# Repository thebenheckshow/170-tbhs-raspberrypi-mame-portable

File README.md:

# 170-tbhs-raspberrypi-mame-portable

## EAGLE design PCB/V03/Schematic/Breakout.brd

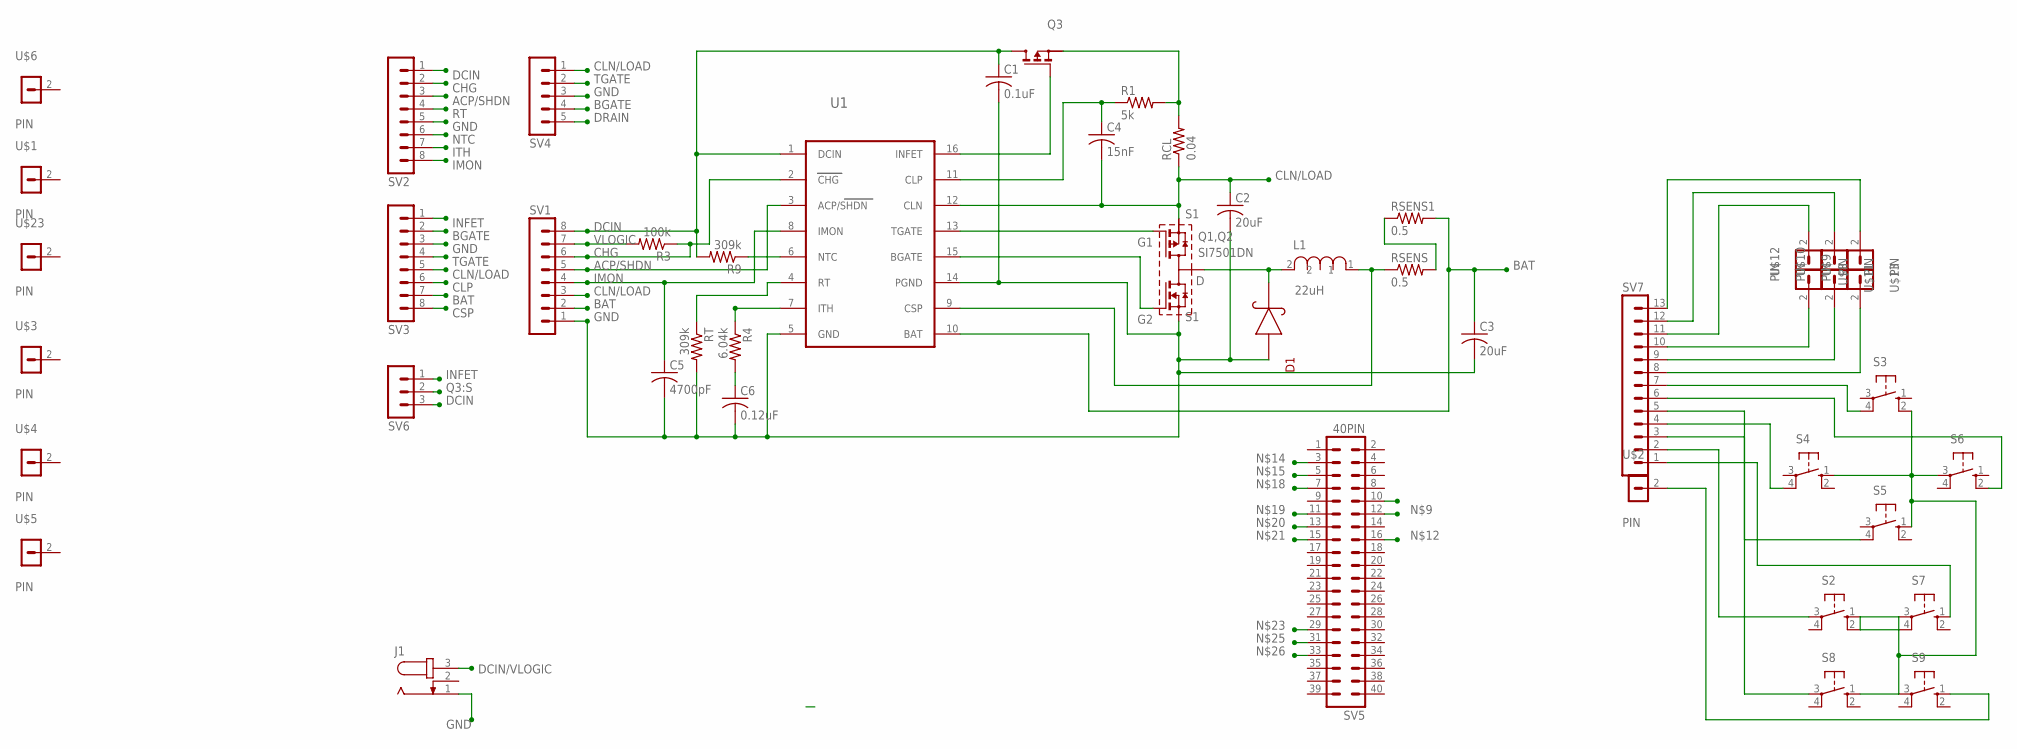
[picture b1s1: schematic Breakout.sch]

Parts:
C1: 0.1uF; C1210
C2, C3: 20uF; C1210
C4: 15nF; C1210
C5: 4700pF; C1210
C6: 0.12uF; C1210
D1: DIODE
J1: JACK-PLUG0; SPC4077
L1: 22uH; POWERINDUCTOR
Q1,Q2: SI7501DN; POWERPAK
Q3: MOSFET; SOT-23
R1: 5k; R1206
R3: 100k; R1206
R4: 6.04k; R1206
R9: 309k; R1206
RCL: 0.04; R1206
RSENS, RSENS1: 0.5; 0612/1632
RT: 309k; R1206
S2, S3, S4, S5, S6, S7, S8, S9: 10-XX; B3F-10XX
SV1, SV2, SV3: MA08-1
SV4: MA05-1
SV5: 40PIN; 40PINHEADDER
SV6: MA03-1
SV7: MA13-1
U1: LTC6004; SSOP-16
U$1, U$2, U$3, U$4, U$5, U$6, U$8, U$9, U$10, U$11, U$12, U$13, U$23: PIN

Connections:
ACP/SHDN: SV1.5, SV2.3, U1.3 (ACP/SHDN)
BAT: C3.1, RSENS1.2, SV1.2, SV3.7, U1.10 (BAT)
BGATE: Q1,Q2.G2, SV3.2, SV4.4, U1.15 (BGATE)
CHG: R3.1, SV1.6, SV2.2, U1.2 (CHG)
CLN/LOAD: C2.1, C4.2, Q1,Q2.S1, RCL.1, SV1.3, SV3.5, SV4.1, U1.12 (CLN)
CLP: C4.1, R1.1, SV3.6, U1.11 (CLP)
CSP: L1.1, RSENS.1, SV3.8, U1.9 (CSP)
DCIN: C1.1, Q3.DRAIN (D), R9.2, SV1.8, SV2.1, SV6.3, U1.1 (DCIN)
DCIN/VLOGIC: J1.3
DRAIN: D1.P$1 (2), L1.2, Q1,Q2.D, SV4.5
GND: C1.2, C2.2, C3.2, C5.2, C6.2, D1.P$2 (1), J1.1, Q1,Q2.S2, RT.2, S2.1 (S), S2.2 (S1), S3.2 (S1), S4.1 (S), S5.1 (S), S6.3, S7.3, S7.4 (P1), S8.1 (S), S9.3, SV1.1, SV2.5, SV3.3, SV4.3, U1.5 (GND), U1.14 (PGND)
IMON: C5.1, SV1.4, SV2.8, U1.8 (IMON)
INFET: Q3.GATE (G), SV3.1, SV6.1, U1.16 (INFET)
ITH: R4.1, SV2.7, U1.7 (ITH)
unnamed: RSENS.2, RSENS1.1
unnamed: SV7.13, U$9.2
unnamed: SV7.12, U$10.2
unnamed: C6.1, R4.2
unnamed: SV7.11, U$12.2
unnamed: SV7.10, U$8.2
unnamed: SV7.9, U$11.2
unnamed: SV7.8, U$13.2
unnamed: S3.4 (P1), SV7.7
unnamed: S6.2 (S1), SV7.6
unnamed: S4.4 (P1), SV7.4
unnamed: S5.4 (P1), SV7.5
unnamed: S8.3, SV7.3
unnamed: S2.3, SV7.2
unnamed: S7.1 (S), SV7.1
unnamed: S9.1 (S), U$2.2
NTC: R9.1, SV2.6, U1.6 (NTC)
Q3:S: Q3.SOURCE (S), R1.2, RCL.2, SV6.2
RT: RT.1, SV2.4, U1.4 (RT)
TGATE: Q1,Q2.G1, SV3.4, SV4.2, U1.13 (TGATE)
VLOGIC: R3.2, SV1.7

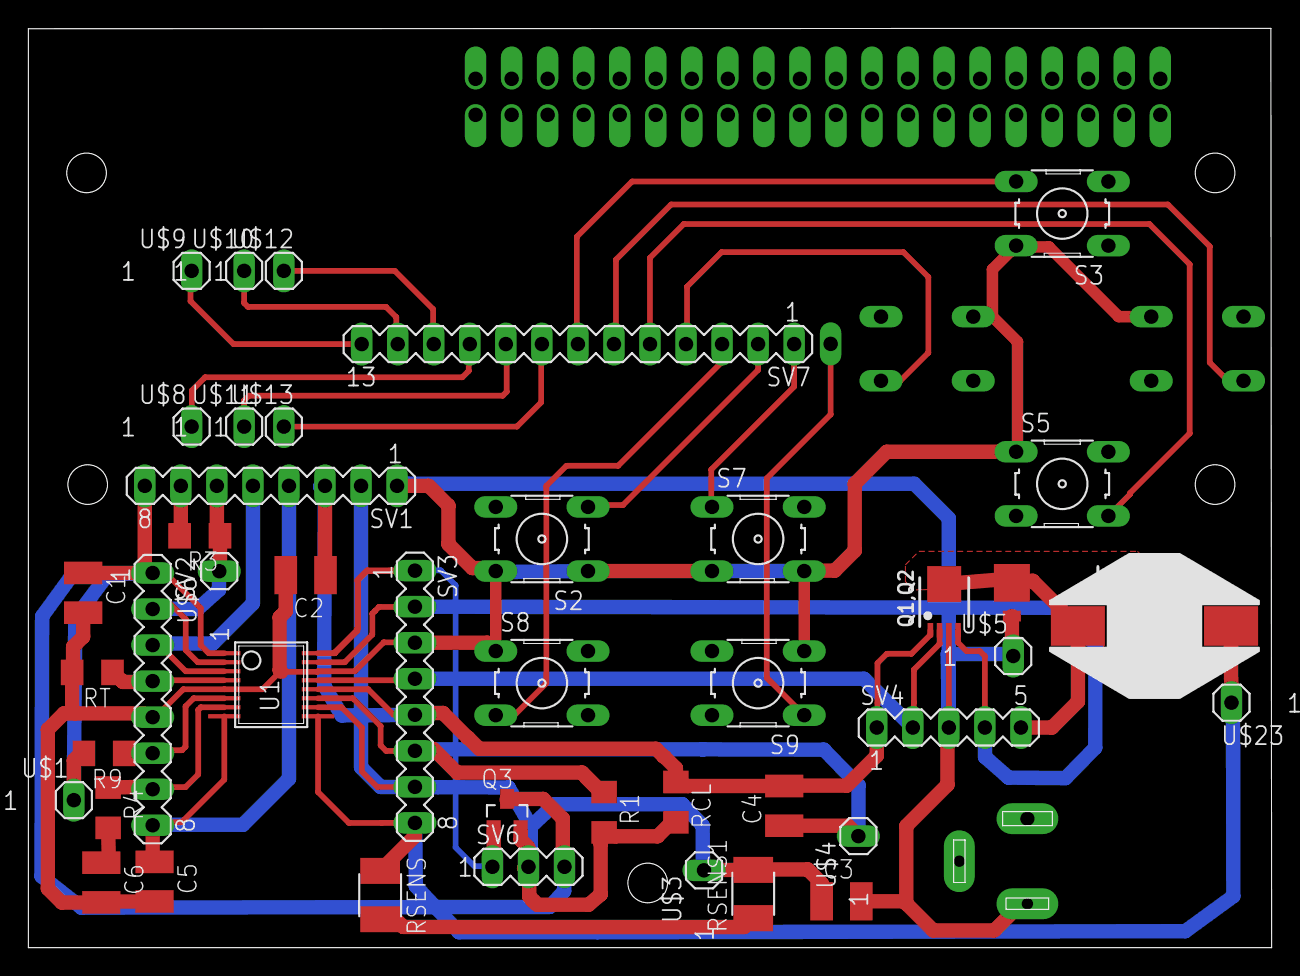
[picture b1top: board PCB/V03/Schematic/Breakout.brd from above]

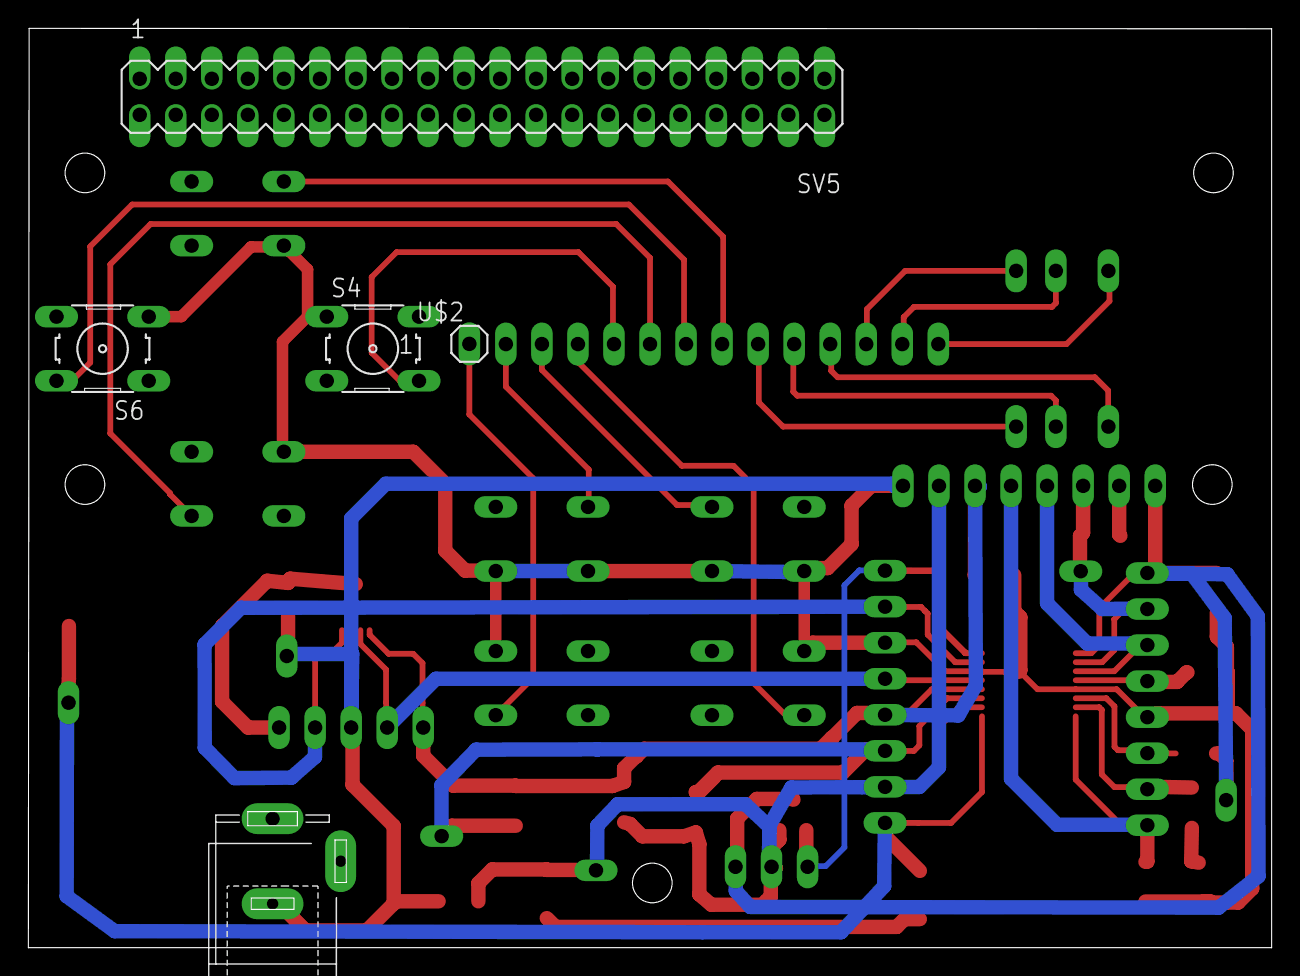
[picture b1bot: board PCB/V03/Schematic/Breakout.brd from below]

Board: 2 copper layers, 87.6 x 64.8 mm, 48 parts (5 on the bottom side), 34 nets.

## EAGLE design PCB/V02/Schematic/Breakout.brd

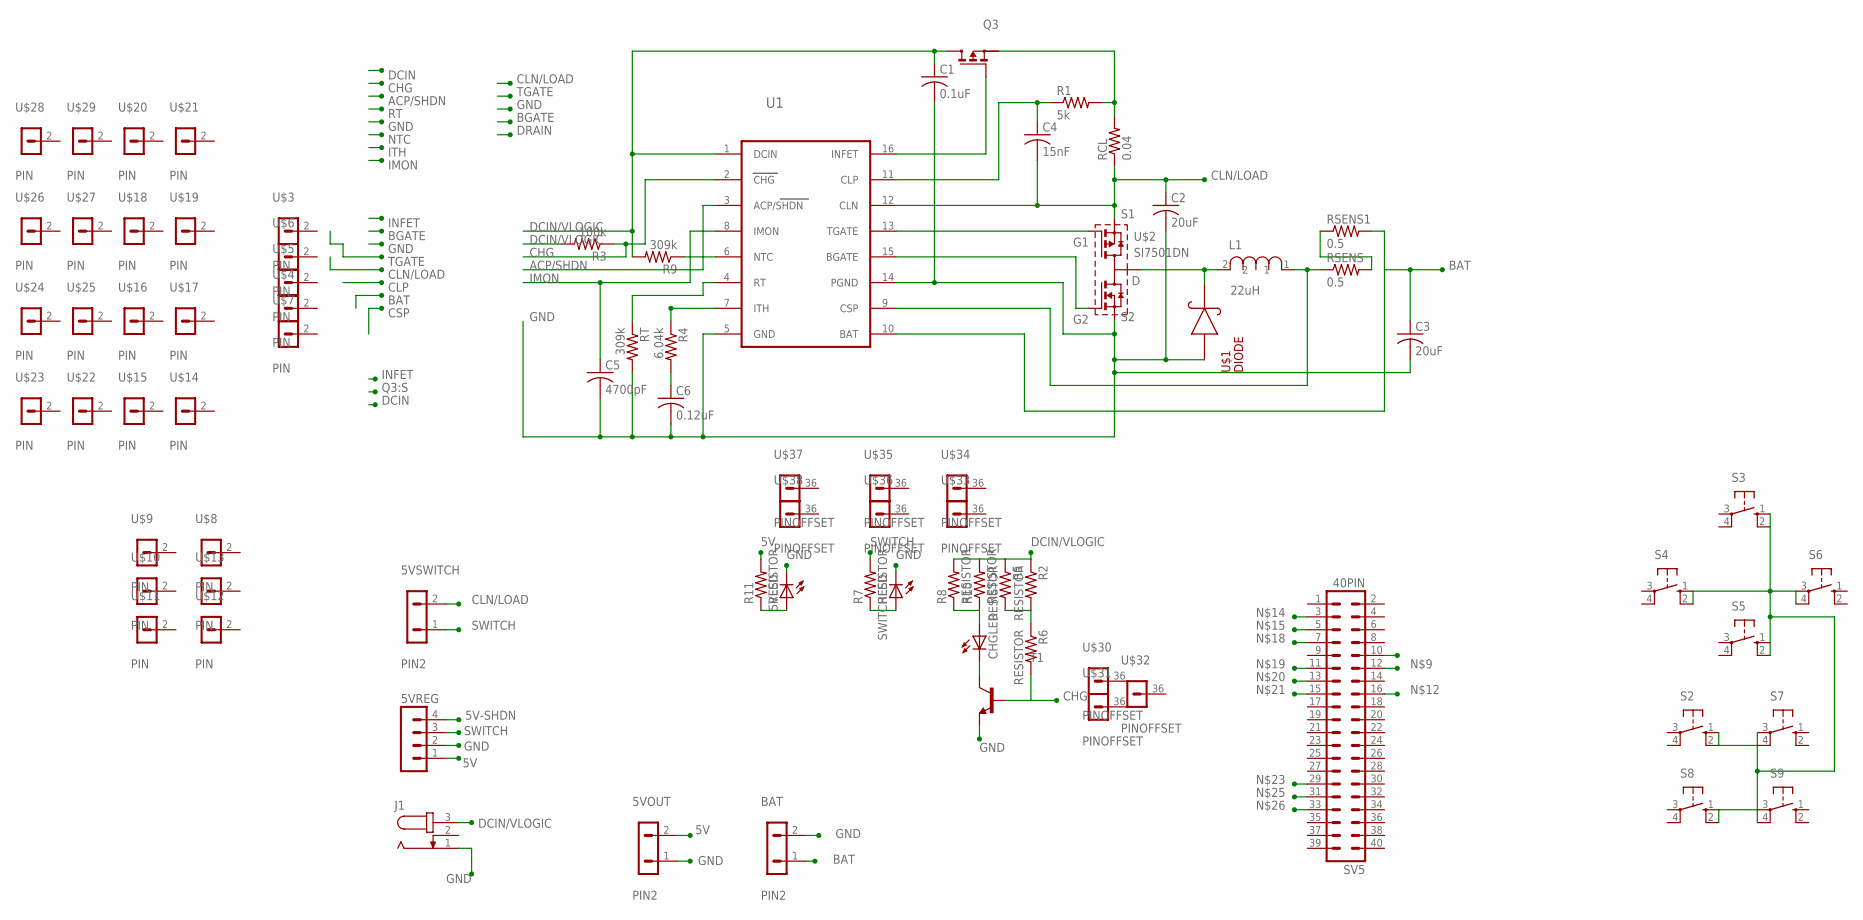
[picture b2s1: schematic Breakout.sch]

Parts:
5VLED: LED5MM
5VOUT, 5VSWITCH: PIN2
5VREG: MA04-1
BAT: PIN2
C1: 0.1uF; C1210
C2, C3: 20uF; C1210
C4: 15nF; C1210
C5: 4700pF; C1210
C6: 0.12uF; C1210
CHGLED: LED5MM
J1: JACK-PLUG0; SPC4077
L1: 22uH; POWERINDUCTOR
Q3: MOSFET; SOT-23
R1: 5k; R1206
R2, R5, R6, R7, R8, R10, R11: RESISTOR
R3: 100k; R1206
R4: 6.04k; R1206
R9: 309k; R1206
RCL: 0.04; R1206
RSENS, RSENS1: 0.5; 0612/1632
RT: 309k; R1206
S2, S3, S4, S5, S6, S7, S8, S9: 10-XX; B3F-10XX
SV5: 40PIN; 40PINHEADDER
SWITCHLED: LED5MM
T1: -NPN-TO92-E1; TO92-E1
U1: LTC6004; SSOP-16
U$1: DIODE
U$2: SI7501DN; POWERPAK
U$3, U$4, U$5, U$6, U$7, U$8, U$9, U$10, U$11, U$12, U$13, U$14, U$15, U$16, U$17, U$18, U$19, U$20, U$21, U$22, U$23, U$24, U$25, U$26, U$27, U$28, U$29: PIN
U$30, U$31, U$32, U$33, U$34, U$35, U$36, U$37, U$38: PINOFFSET; PINOFFST

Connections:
5V: 5VOUT.2, 5VREG.1, R11.1 (2)
5V-SHDN: 5VREG.4
ACP/SHDN: U1.3 (ACP/SHDN)
BAT: BAT.1, C3.1, RSENS1.2, U1.10 (BAT)
BGATE: U1.15 (BGATE), U$2.G2
CHG: R3.1, R6.1 (2), T1.2 (B), U1.2 (CHG)
CLN/LOAD: 5VSWITCH.2, C2.1, C4.2, RCL.1, U1.12 (CLN), U$2.S1
CLP: C4.1, R1.1, U1.11 (CLP)
CSP: L1.1, RSENS.1, U1.9 (CSP)
DCIN/VLOGIC: C1.1, J1.3, Q3.DRAIN (D), R2.2 (1), R3.2, R5.2 (1), R8.1 (2), R9.2, R10.1 (2), U1.1 (DCIN)
DRAIN: L1.2, U$1.P$1 (2), U$2.D
GND: 5VLED.K (C), 5VOUT.1, 5VREG.2, BAT.2, C1.2, C2.2, C3.2, C5.2, C6.2, J1.1, RT.2, S2.1 (S), S2.2 (S1), S3.1 (S), S3.2 (S1), S4.1 (S), S4.2 (S1), S5.1 (S), S5.2 (S1), S6.3, S6.4 (P1), S7.3, S7.4 (P1), S8.1 (S), S8.2 (S1), S9.3, S9.4 (P1), SWITCHLED.K (C), T1.3 (E), U1.5 (GND), U1.14 (PGND), U$1.P$2 (1), U$2.S2
IMON: C5.1, U1.8 (IMON)
INFET: Q3.GATE (G), U1.16 (INFET)
ITH: R4.1, U1.7 (ITH)
unnamed: RSENS.2, RSENS1.1
unnamed: R2.1 (2), R5.1 (2), R6.2 (1)
unnamed: CHGLED.A, R8.2 (1), R10.2 (1)
unnamed: C6.1, R4.2
unnamed: R7.2 (1), SWITCHLED.A
unnamed: CHGLED.K (C), T1.1 (C)
unnamed: 5VLED.A, R11.2 (1)
NTC: R9.1, U1.6 (NTC)
Q3:S: Q3.SOURCE (S), R1.2, RCL.2
RT: RT.1, U1.4 (RT)
SWITCH: 5VREG.3, 5VSWITCH.1, R7.1 (2)
TGATE: U1.13 (TGATE), U$2.G1

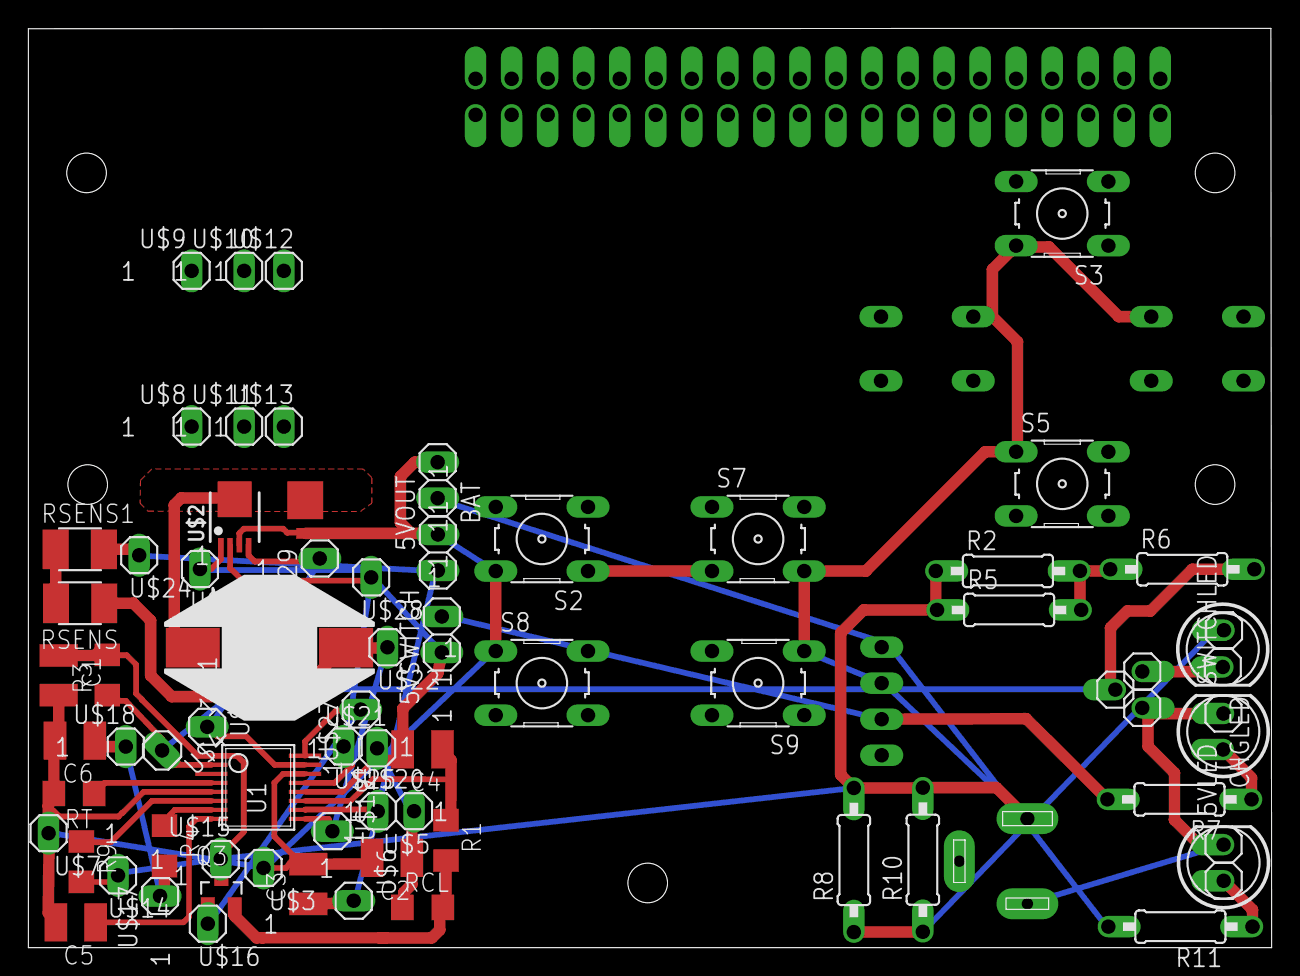
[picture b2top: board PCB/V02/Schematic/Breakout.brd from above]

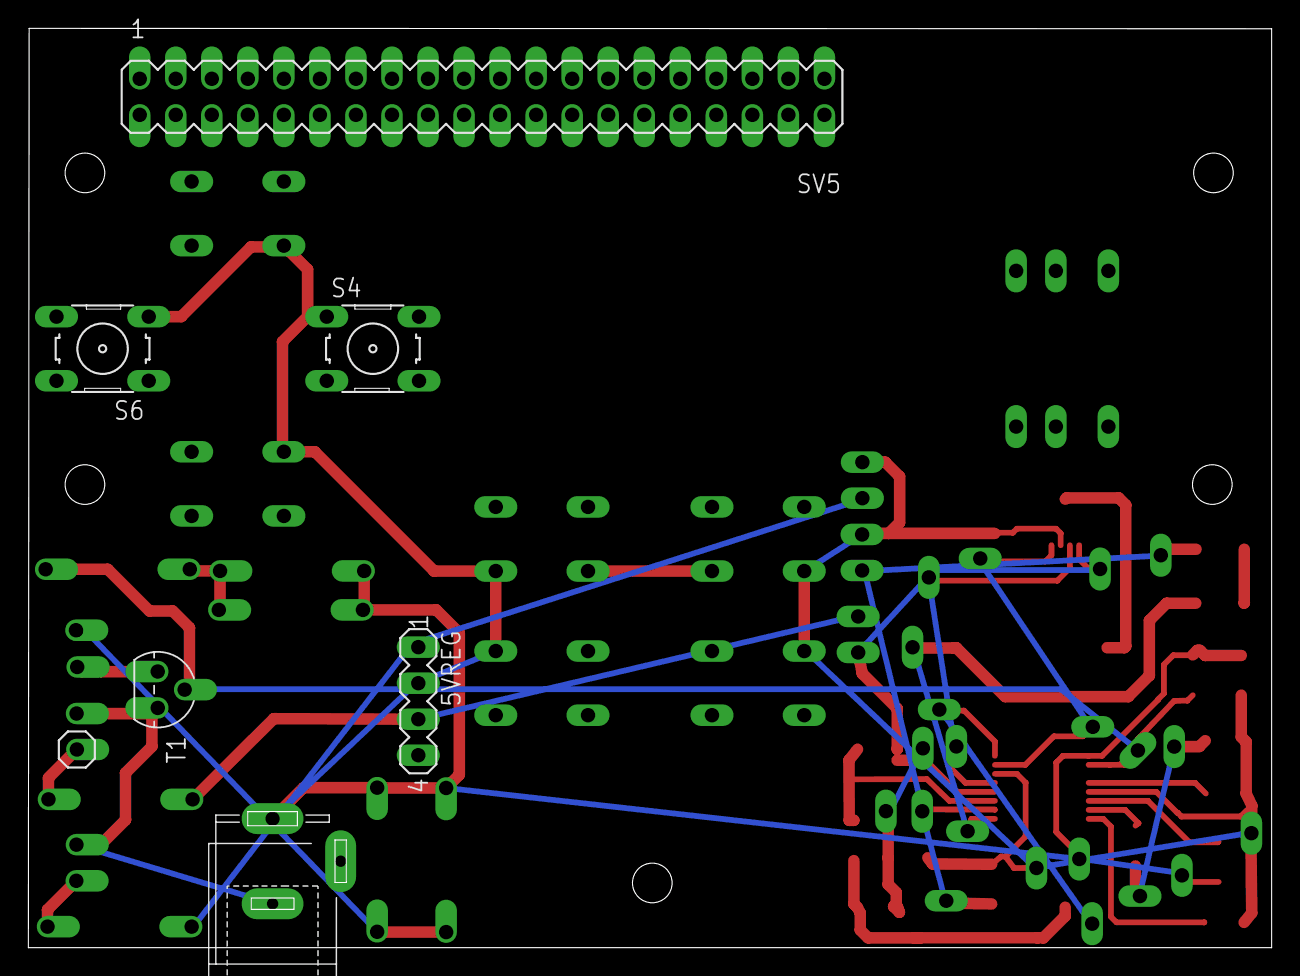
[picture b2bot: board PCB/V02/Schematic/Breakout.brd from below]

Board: 2 copper layers, 87.6 x 64.8 mm, 80 parts (7 on the bottom side), 25 nets.

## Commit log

2015-08-13 Initial commit.
